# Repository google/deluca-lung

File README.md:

# deluca-lung

## Getting started
Instructions to provide to students: run the following commands
```
pip install deluca-lung
jupyter notebook
```

Navigate to the notebook `demo/2021-07-18 controller demo.ipynb` and run the cells.

## Setting up Raspberry Pi
- Create a Raspberry Pi OS image via [this](https://github.com/MinRegret/rpi-gadget-image-creator)

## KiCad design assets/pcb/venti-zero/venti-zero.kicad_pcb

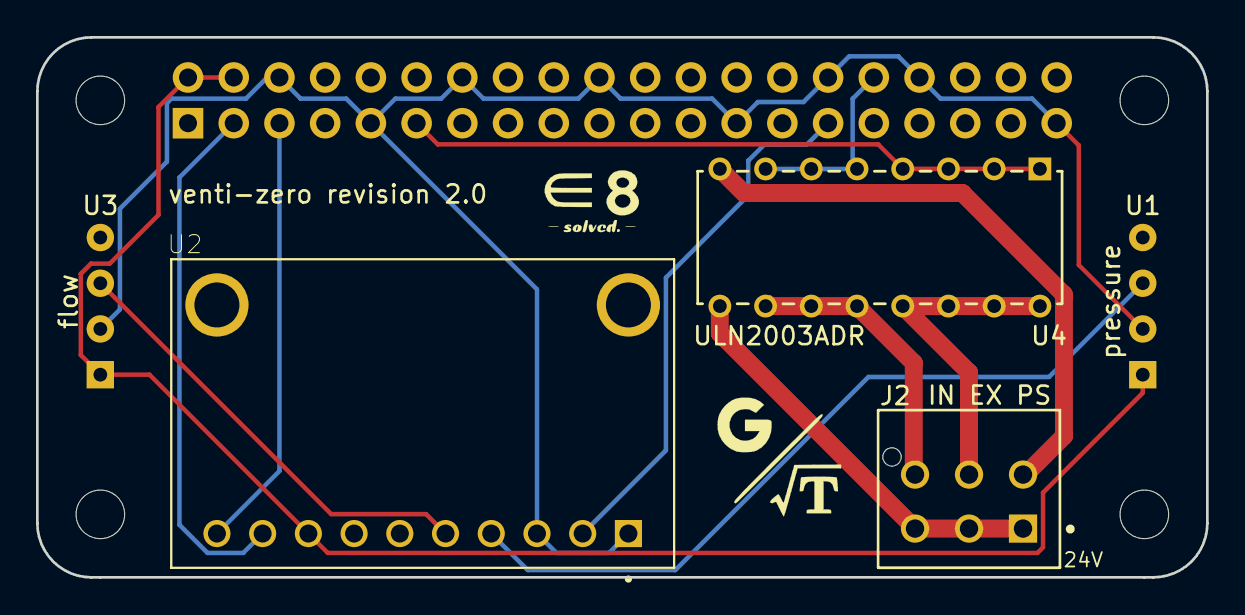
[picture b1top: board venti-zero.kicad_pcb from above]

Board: 2 copper layers, 65.0 x 30.0 mm, 10 parts (1 on the bottom side), 13 nets.

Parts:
H1, H2, H3, H4: MountingHole; MountingHole_2.7mm_M2.5_uHAT_RPi
J1: GPIO_CONNECTOR; PinSocket_2x20_P2.54mm_Vertical_Centered_Anchor
J2: 206832-0601; Molex-206832-0601-MFG
U1: pressure; MINI-P-Sensor-Horizontal
U2: ADS1115IDGSR; ADS1115
U3: flow; MINI-P-Sensor-Horizontal
U4: ULN2003ADR; ULN2003A

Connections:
+5V: J1.2, J1.4, U1.1, U2.8, U3.1
+24V: J2.1, J2.3, J2.5, U4.9
/GPIO2_SDA1: J1.3, U2.9
/GPIO3_SCL1: J1.5, U2.10
/GPIO5: J1.29, U2.2
/GPIO12: J1.32, U4.5, U4.6, U4.7
/GPIO17: J1.11, U4.1, U4.2, U4.3, U4.4
GND: J1.6, J1.9, J1.14, J1.20, J1.25, J1.30, J1.34, J1.39, U1.2, U2.1, U2.3, U3.2
GND1: J2.2, U4.8
unnamed: J2.4, U4.13, U4.14, U4.15, U4.16
unnamed: J2.6, U4.10, U4.11, U4.12
unnamed: U1.3, U2.4
unnamed: U2.5, U3.3

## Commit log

2021-07-19 Add sim/controller pkls
2021-08-16 Update version
2021-08-16 Add data directory
2021-08-16 bump version
2021-08-18 Pin deluca

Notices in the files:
assets/pcb/venti-zero/venti-zero.kicad_pcb:
Copyright 2021 Google LLC
License: Apache 2.0
parts and their libraries:
Copyright 2016 Accelerated Designs. All rights reserved.
